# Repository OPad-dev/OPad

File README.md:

<div align="center">

<picture>
  <source media="(prefers-color-scheme: dark)" srcset="docs/assets/wordmark-dark.svg">
  
</picture>

### A low-latency three-key osu! keypad with a touchscreen, that is just a keyboard until you want more.

**[Download](https://github.com/OPad-dev/OPad/releases)** ·
**[Documentation](docs/index.md)** ·
[Get started](docs/start/what-you-need.md) ·
[Troubleshooting](docs/troubleshooting.md) ·
[Code signing policy](#code-signing-policy) ·
[Privacy](#privacy)

</div>

---

OPad turns a **Waveshare ESP32-S3-Touch-LCD-2** and two switches into a
competition-grade keypad for osu! and osu!lazer. It is a plain **1000 Hz USB
HID keyboard**: plug it into any Linux or Windows 10/11 machine and it types,
with no driver and no setup. The optional desktop app adds live gameplay stats
on the pad's screen, a screen designer, lifetime key counters, Hall Effect
calibration and one-click firmware updates.

## Highlights

|  |  |
|---|---|
| ⚡ **Latency always wins** | Keys go straight from the switch to the USB report. The screen, storage, tray and tosu are never on that path, and anything that measurably adds latency or jitter is cut. |
| 🔌 **Works with nothing installed** | Standard HID keyboard (`Z` / `X` by default). The desktop software only adds features. |
| 👆 **The touchscreen is a fourth button** | During a map a resting finger is Quick Retry. Outside a map, swipes change the volume or the track. |
| 📊 **Live telemetry** | With [tosu](https://github.com/KotRikD/tosu), the pad shows PP, accuracy, combo and more, in layouts you design yourself. |
| 🧲 **Mechanical or Hall Effect** | MX switches wired by hand, or the OPad V3 carrier with MX or Hall Effect modules, guided calibration and Rapid Trigger. |
| 🛟 **Can't be bricked by an update** | Updates go to the other flash slot and roll back on their own if the pad doesn't come back. No BOOT or RESET buttons, ever. |
| 🔁 **App and pad update independently** | Any app version talks to any pad version; they negotiate. |
| 🚫 **Every key comes from a finger** | No macros, auto-tap or host-injected keys. Not even as an option. |

## Quick start

1. **Wire two switches** between header **P2 pin 11** (GPIO 14, `Z`) /
   **pin 12** (GPIO 9, `X`) and **GND** (pin 13 or 2), or assemble the V3
   carrier. → [Wiring the keys](docs/build/wiring-the-keys.md)
2. **Plug it in.** It types immediately. → [First connection](docs/start/first-connection.md)
3. **Optional: install the app** for the screen, counters and updates.
   → [Install the app](docs/start/install-the-app.md)

| System | Download from [Releases](https://github.com/OPad-dev/OPad/releases) |
|---|---|
| Windows 10/11 | `OPad-Windows-Setup-<version>.exe` |
| Debian, Ubuntu, Pop!_OS | `OPad-Linux-Debian-Ubuntu-<version>.deb` |
| Fedora, RHEL, Alma, Rocky | `OPad-Linux-Fedora-<version>.rpm` |
| Arch | `OPad-Linux-Arch-<version>.pkg.tar.zst` |
| Any other Linux | `OPad-Linux-<version>.AppImage` |

> [!NOTE]
> The Windows installer is not code-signed yet, so SmartScreen warns about it
> (**More info → Run anyway**). Each release page lists the SHA-256 of every
> file if you'd rather verify the download. See the
> [code signing policy](#code-signing-policy).

## How it fits together

```mermaid
flowchart LR
    osu["osu! / osu!lazer"] -. read by .-> tosu["tosu"]
    tosu -- WebSocket --> daemon["opad-daemon<br/>settings · stats · updates"]
    gui["opad-gui<br/>tray · designer · diagnostics"] <-- IPC --> daemon
    cli["opadctl"] <-- IPC --> daemon
    daemon <-- "USB serial (CDC)" --> pad["OPad<br/>ESP32-S3 + 2&quot; touchscreen"]
    pad == "USB HID keyboard, 1000 Hz" ==> os["Your computer"]
```

The keyboard link (thick arrow) needs none of the boxes above it.
[Architecture](docs/explanation/architecture.md) explains the rest.

## Documentation

The full documentation lives in [`docs/`](docs/index.md) and is also
published as a website.

| | |
|---|---|
| 🚀 **Getting started** | [What you need](docs/start/what-you-need.md) · [Wiring](docs/build/wiring-the-keys.md) · [First connection](docs/start/first-connection.md) · [Install the app](docs/start/install-the-app.md) |
| 🧭 **Guides** | [Update firmware](docs/guides/update-firmware.md) · [Touchscreen & swipes](docs/guides/touchscreen-and-swipes.md) · [Screen layouts](docs/guides/customize-screen-layout.md) · [Hall Effect calibration](docs/guides/calibrate-hall-effect.md) · [tosu](docs/guides/use-with-tosu.md) · [Backup](docs/guides/backup-and-restore.md) |
| 🛟 **When something's wrong** | [Troubleshooting](docs/troubleshooting.md) · [Recovery & reflashing](docs/recovery.md) |
| 📖 **Reference** | [`opadctl`](docs/reference/opadctl.md) · [GUI](docs/reference/gui.md) · [Device settings](docs/reference/device-settings.md) · [Pinout](docs/reference/pinout.md) · [Serial protocol](docs/reference/serial-protocol.md) |
| 💡 **How it works** | [Architecture](docs/explanation/architecture.md) · [Latency](docs/explanation/latency.md) · [Updates & rollback](docs/explanation/updates-and-rollback.md) · [Hall Effect](docs/explanation/hall-effect.md) |
| 🛠️ **Contributing** | [Developer hub](docs/develop/index.md) · [Building](docs/develop/building.md) · [Testing](docs/develop/testing.md) · [AGENTS.md](AGENTS.md) |

Documentation is also available in [Spanish](docs/es/index.md).

## Building from source

```bash
# Desktop suite (daemon, GUI, opadctl)
cd desktop && cargo build --release

# Firmware (ESP-IDF v5.5.2)
cd firmware && idf.py set-target esp32s3 build

# Flash it over USB: the other OTA slot, rolls back if it never enumerates
opadctl pad flash firmware/build/opad-firmware.bin
```

System packages, `make install`, tests and CI are covered in
[Building from source](docs/develop/building.md) and
[Testing](docs/develop/testing.md). Contributions are welcome: read
[AGENTS.md](AGENTS.md) first. It holds the product rules every change keeps.

---

## Code signing policy

Free code signing provided by [SignPath.io](https://about.signpath.io), certificate by [SignPath Foundation](https://signpath.org).

The Windows programs (`opad-gui.exe`, `opad-daemon.exe`, `opadctl.exe`) and the Windows installer are built from this repository by GitHub Actions (`.github/workflows/release-app.yml`) and signed only after a maintainer approves each release. Until the SignPath Foundation certificate is in place, Windows releases are published unsigned.

- Committers and reviewers: [GFerreiroS](https://github.com/GFerreiroS)
- Approvers: [GFerreiroS](https://github.com/GFerreiroS)

The installer also contains two programs that are not built from this repository's code and are not signed by this project: `espflash.exe` ([esp-rs/espflash](https://github.com/esp-rs/espflash), the upstream release binary) and `tosu.exe` ([tosu](https://github.com/KotRikD/tosu), built from upstream source).

Privacy policy: see [Privacy](#privacy) below.

## Privacy

OPad collects no personal data and has no telemetry or analytics. The desktop app makes these network requests, and no others:

- **Update check**, once a day while the app's background service runs, and whenever you press *Check now*: it downloads the public release list from `https://updates.opad.dev/` (served by GitHub Pages). The request carries the app's version in its User-Agent (`opad/<version>`) and nothing about you or your pad. Turning off automatic updates in **Settings → Updates** stops installs, not this check.
- **Downloads** of an update you accept (or of tosu, if its automatic updates are on), from GitHub Releases.
- **tosu**, which the app runs, serves osu!'s game state on your own computer (`127.0.0.1`) and does not send it anywhere. When it starts, tosu asks GitHub whether a newer tosu exists; OPad turns its self-update off, so nothing is downloaded.

GitHub, which hosts the update list and the downloads, sees your IP address as it does for any website; see [GitHub's privacy statement](https://docs.github.com/site-policy/privacy-policies/github-general-privacy-statement). Everything the app stores (settings, statistics, backups) stays on your computer and your pad.

## Third-party software

OPad bundles or interacts with the following third-party software:

- **[tosu](https://github.com/KotRikD/tosu)** by Mikhail Babynichev and the tosu contributors, under the [LGPL-3.0](licenses/tosu/LICENSE) ([notice](licenses/tosu/NOTICE)). Under the LGPL you may replace the bundled tosu with your own build: point the `OPAD_TOSU_PATH` environment variable at it, or set an external path in the GUI under **Settings → tosu**.
- **[espflash](https://github.com/esp-rs/espflash)**, bundled with the desktop packages as the upstream release binary.

## Licence

OPad is free and open source, software and hardware:

- **Software**: the firmware, the desktop app (daemon, GUI, CLI), the protocol, the scripts and the documentation, under the [GNU General Public License v3.0 or later](LICENSE) (`GPL-3.0-or-later`).
- **Hardware**: everything in [`hardware/`](hardware/) (the PCB designs, footprints and symbols, the enclosure CAD and the production files), under the [CERN Open Hardware Licence v2, Strongly Reciprocal](hardware/LICENSE) (`CERN-OHL-S-2.0`). The scripts in `hardware/` that generate and check those files are software, under `GPL-3.0-or-later`.

You may build, modify and sell OPad. If you distribute a modified version, of the software or of the hardware, you must publish its source under the same licence. Every file's licence is recorded in [`REUSE.toml`](REUSE.toml).

Third-party components keep their own open licences and ship with their notices:

- [tosu](licenses/tosu/LICENSE) (LGPL-3.0), built from upstream source and bundled with the desktop packages, see above. Not stored in this repository.
- [Montserrat](desktop/gui/assets/fonts/Montserrat-OFL.txt) fonts embedded in the GUI (SIL Open Font License 1.1).
- [nanopb](firmware/main/protocol/nanopb/LICENSE.txt) protobuf runtime vendored in the firmware (zlib licence).

Libraries pulled in at build time (Rust crates, ESP-IDF components such as LVGL and TinyUSB) are not stored here and are used under their own permissive licences.

The firmware's easter-egg animation (`firmware/main/ui/easter_egg_gif.h`) is the one exception: it was made from images found online whose author and licence are unknown, and no rights to it are granted. If you hold the rights and want it credited or no longer used, open an issue or write to the contact in [`SECURITY.md`](SECURITY.md); it is then credited, or removed from the firmware ([`LICENSES/LicenseRef-Unknown-ThirdParty.txt`](LICENSES/LicenseRef-Unknown-ThirdParty.txt)).

## Trademark

OPad is an independent open-source hardware and software project. It is not affiliated with, endorsed by, or sponsored by ppy Pty Ltd or osu!. "osu!" is a registered trademark of ppy Pty Ltd.

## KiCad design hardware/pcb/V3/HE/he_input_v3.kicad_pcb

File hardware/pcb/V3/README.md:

# OPad V3 PCBs

| Board | Folder | Size | Status |
|---|---|---|---|
| Controller carrier V3 | `Carrier/` | 35.0 × 48.2 mm (the V1 outline plus a lug in the window for the USB cable) | Built; works on the bench (2026-11-20) |
| USB board V3 | `USB/` | 20.0 × 22.0 mm | Built; works on the bench (2026-11-20) |
| MX input module V3 | `MX/` | 71.05 × 24.0 mm, 3 keys | Built; works on the bench (2026-11-20) |
| HE input module V3 | `HE/` | 71.05 × 24.0 mm, 3 keys | Built; works on the bench (2026-11-20) |

These replace every V1/V2 board (decisions H10–H18 and section 4.2 in
`docs/specs/hardware-redesign-brief.md`). They are built and run on the owner's
bench with the firmware on `main`: board test, three keys on both modules, HE V3
calibration, key 3 and latency (`docs/testing-checklist.md` HW-06 to HW-15, and
`docs/history/2026-11-20-v3-modules-handoff.md`). An MX V3 module on a turned-over
module cable is not read; every pad ships with the type B cable.

## What is different from V1

- **Module cable:** a 14-way, 1.0 mm FFC replaces the JST SH 8-pin. It is reversible
  (a reversed cable only swaps signals between ESP32 pins, see Cables).
- **USB-C on its own board** at the case's rear wall (H18). It has ESD protection, a VBUS
  ferrite and capacitors, and a Schottky so a cable in the Waveshare's own port cannot
  feed this one. An 8-way FFC that reads the same from either end takes 5 V, D+ and D−
  to the carrier, which passes them to P1-14, P1-11 (GPIO20) and P1-12 (GPIO19).
  The case seats it on pins in its two M2 holes and clamps it from above; stops and the
  rear wall take the plug's push and pull, so the header sockets never do. The path is passive, so flashing and recovery work over it as over
  the Waveshare's own port.
- **The carrier's USB connector** sits on a lug in the window's USB-end rear corner,
  mouth on the USB-end edge: P1's sockets fill the rear edge, and the lug keeps clear of
  the M2 hole at the USB-end rear corner. (The V3 and V4 cases do not use that hole: the USB
  board lies under it, so a support presses the rear rail instead.)
- **Three keys** on both modules, and **four corner holes** for the case's locating pins.
- **HE:**
  - The ADC is an **ADS7028** (C880341), the ADS7038's sibling. It has the same pins,
    registers, averaging and CRC, and it is in JLCPCB's assembly stock. The ADS7038 is
    only on LCSC.
  - An **LP5907 LDO** powers the sensors and the ADC reference from the cable's 5 V,
    not from the Waveshare's buck-converter 3V3.
  - CS has a pull-up, and the SPI lines have ESD protection.
- **Every part is on one side:** the top of the carrier and the USB board, the bottom of
  the modules.

## Cables

### Module (14-way FFC, 1.0 mm, type B, 80 mm in the V3 and V4 cases)

| Contact | 1 | 2 | 3 | 4 | 5 | 6 | 7 | 8 | 9 | 10 | 11 | 12 | 13 | 14 |
|---|---|---|---|---|---|---|---|---|---|---|---|---|---|---|
| Carrier | GND | 5V | 3V3 | GPIO8 | GPIO6 | GND | GPIO2 | GPIO4 | GND | GPIO10 | GPIO7 | 3V3 | 5V | GND |
| HE | GND | 5V | 3V3 | ID | MISO | GND | SCLK | MOSI | GND | CS | – | 3V3 | 5V | GND |
| MX | GND | – | 3V3 | ID | KEY3 | GND | – | – | GND | KEY1 | KEY2 | 3V3 | – | GND |

A reversed cable connects contact k to 15 − k. Power and ground still meet power and
ground. The module's ID arrives on GPIO7 instead of GPIO8 (both are ADC1 pins), and the
firmware swaps the other pins in the GPIO matrix. `hardware/verify/tests/test_system.py`
follows every pin both ways round. MX keeps KEY1 = GPIO10 and KEY2 = GPIO7, as on V1.

Module IDs: MX V3 = 47k/100k = 2.24 V, HE V3 = 100k/100k = 1.65 V (the class HE V2
reserved, since the ADC and pins are the same). Firmware cut-offs: 0.68 / 1.35 / 1.95 / 2.6 V.

### USB (8-way FFC, 1.0 mm, type A, 80 mm in the V3 and V4 cases)

| Contact | 1 | 2 | 3 | 4 | 5 | 6 | 7 | 8 |
|---|---|---|---|---|---|---|---|---|
| USB board and carrier | GND | 5V | D− | D+ | D+ | D− | 5V | GND |

The pinout reads the same from either end, so a reversed cable (k to 9 − k) meets the
same nets. D+ and D− each use two conductors, joined on both boards. The two 5V contacts
carry 1 A together (0.5 A each, connector datasheet). The connectors are a different width
from the module's, so the two cables cannot be swapped. `test_system.py` follows the jack's
D+, D− and 5 V to GPIO20, GPIO19 and P1-14 with the cable both ways round.

## Checks (MX 2026-10-23; carrier, USB, HE 2026-10-29)

| Check | Carrier | USB | MX | HE |
|---|---|---|---|---|
| KiCad ERC, DRC with zones refilled, schematic parity | 0 | 0 | 0 | 0 |
| `hardware/verify` (fab files against the intended netlist, datasheet pin drawings, JLCPCB's own part models at the CPL) | 0 errors | 0 errors | 0 errors | 0 errors |
| `hardware/verify/tests/test_system.py` (cables both ways, ID margins) | all pass | all pass | all pass | all pass |

- **Ferrite C107335 (carrier, HE):** replaces C1002 (Sunlord GZ1608D601TF), which LCSC no
  longer lists (product page not found, 2026-10-29). Same 600 Ω @ 100 MHz, 1 A instead of
  200 mA. It is an Extended part at JLCPCB, so it adds a setup fee.

- **AFA07-S08 (C262714):** JLCPCB's model draws the fitting nails 3.3 mm tall and 0.63 mm
  nearer the contacts than the maker's drawing (the same drawing as the 14-way's). Our
  pads follow the drawing. The CPL is aligned on the contacts, and the model's nails are
  allowed 0.8 mm (`MECH_TOL` in `export_v3.py`, `jlc_mech_tol` in `devices.py`).

- **CPL:** `export_v3.py` writes the CPL by fitting JLCPCB's own footprint of every part
  onto our pads. Every polarised bottom-side part therefore sits at 0° or 180°. That
  is the case the evidence covers (`hardware/verify/opadverify/jlc.py`). For that reason
  the Hall sensors are turned a quarter from V1.1; the generator asserts that their pads
  are V1.1's layout rotated, never mirrored.
- **Sensor keepout:** a 3 × 3 mm copper keepout sits round each Hall sensor, as on V1.1.

## Files

```
V3/
├── lib/                 footprints (new ones drawn from the makers' drawings) and symbols
├── Carrier/ USB/ MX/ HE/  KiCad projects, route.json (stitching vias, power track widths), production/
└── scripts/
    ├── v3lib.py         library: footprints, symbols
    ├── generate_v3.py   schematics and placed boards (overwrites the routing)
    ├── route_v3.py      Freerouting 1.9.0, retried until DRC has no error and nothing unconnected
    └── export_v3.py     V1's export_production.py checks and files, with the JLCPCB-model CPL
```

```
python3 hardware/pcb/V3/scripts/generate_v3.py [carrier] [usb] [mx] [he]
python3 hardware/pcb/V3/scripts/route_v3.py Carrier|USB|MX|HE
python3 hardware/pcb/V3/scripts/export_v3.py [Carrier] [USB] [MX] [HE]
cd hardware/verify && ../../.tools/venv/bin/python -m opadverify golden/he_v3.toml   # and carrier_v3, usb_v3, mx_v3
```

## Before ordering more

1. **Case:** `hardware/3d/custom_case/V3` was printed and fits these boards; the
   latest small changes to it have not been printed. `hardware/3d/custom_case/V4`, the
   case to ship, is V3 inside a new outside: its fit check passes, it is not printed yet.
2. **JLCPCB preview:** check every part sits on its pads before paying. The checker
   predicts no turning is needed (`-v` prints where pin 1 of each polarised part must be).

## Parts (JLCPCB, all in assembly stock on 2026-10-23)

| Board | Part | LCSC |
|---|---|---|
| carrier, MX, HE | JUSHUO AFA07-S14FCA-00 FFC connector | C262720 |
| carrier, USB | JUSHUO AFA07-S08FCA-00 FFC connector (in stock 2026-10-28) | C262714 |
| USB | HRO TYPE-C-31-M-12 USB-C | C165948 |
| carrier | XUNPU FH2.54-09-14PZD 1×14 socket, 8.5 mm (×2) | C7500781 |
| carrier, USB, HE | ProTek SRV05-4-P-T7 ESD array | C85364 |
| USB | Murata BLM18PG121SN1D ferrite, 2 A | C14709 |
| USB | B5817W Schottky (JLCPCB's model: pad 1 anode, pad 2 cathode) | C7420328 |
| carrier, HE | TDK MPZ1608S601ATA00 ferrite, 1 A | C107335 |
| MX | Kailh CPG151101S11 hot-swap socket (×3) | C41430893 |
| HE | TI DRV5055A3QDBZR Hall sensor (×3) | C266128 |
| HE | TI ADS7028IRTER ADC | C880341 |
| HE | TI LP5907MFX-3.3 LDO | C80670 |

The full lists, with the passives, are in each board's `production/jlcpcb/*-BOM-JLCPCB.csv`.
The cables are not assembled. The connectors are bottom contact, so the cable type is
fixed by the route in the V3 case (`hardware/3d/custom_case/V3/README.md`, The cables):
a 14-way, 1.0 mm FFC, **type B** (contacts on opposite sides, "reverse"), 80 mm
(LCSC C54350068), and an
8-way, 1.0 mm FFC, **type A** (contacts on the same side), 80 mm (LCSC C54350099; the route is about 66 mm with
both ends in their connectors, and the extra bows up in the space beside the stack).

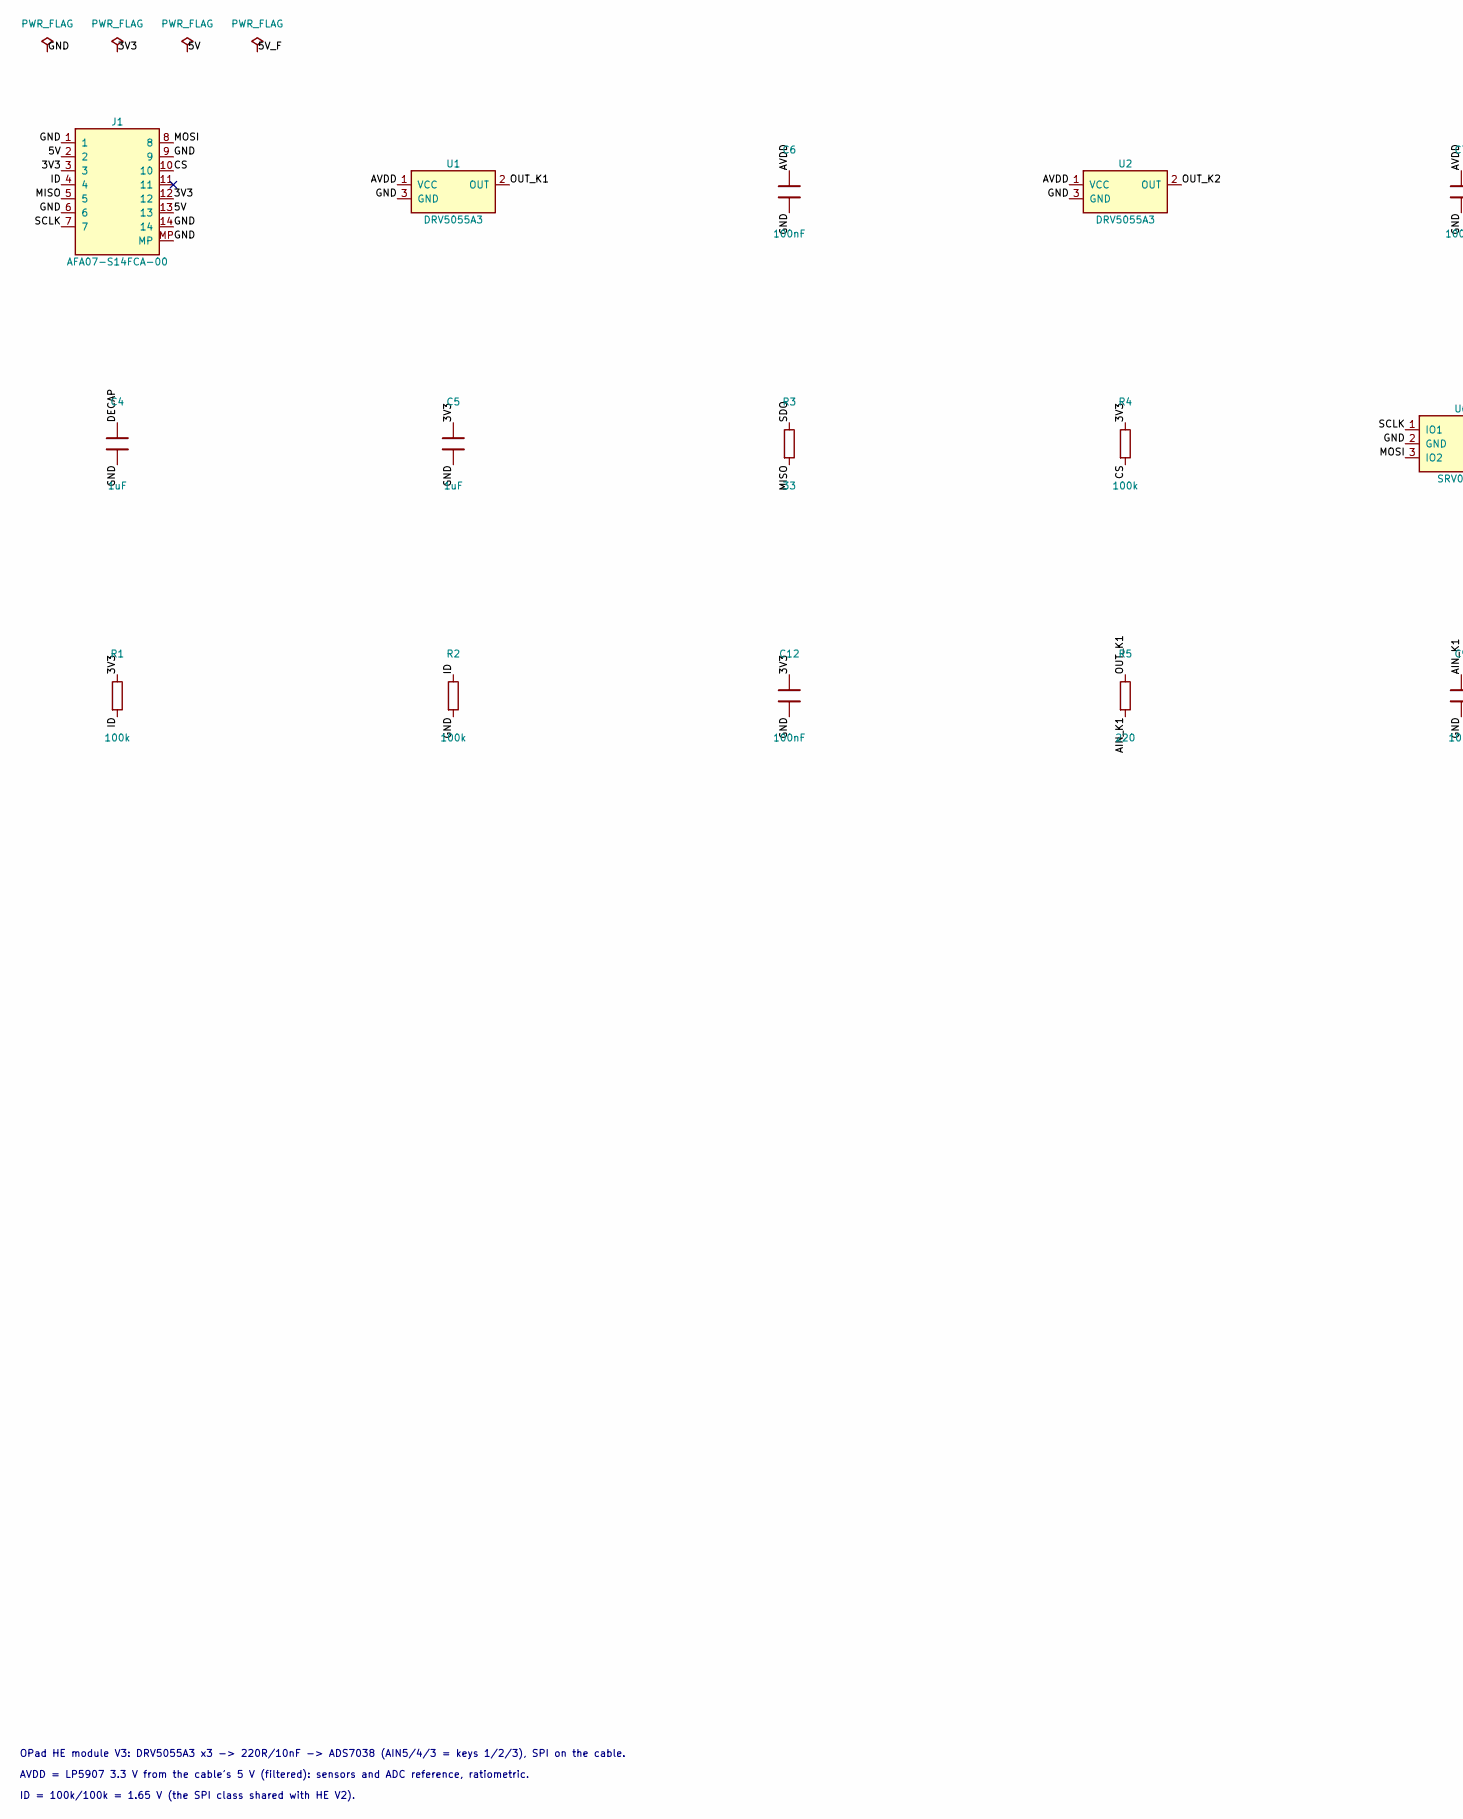
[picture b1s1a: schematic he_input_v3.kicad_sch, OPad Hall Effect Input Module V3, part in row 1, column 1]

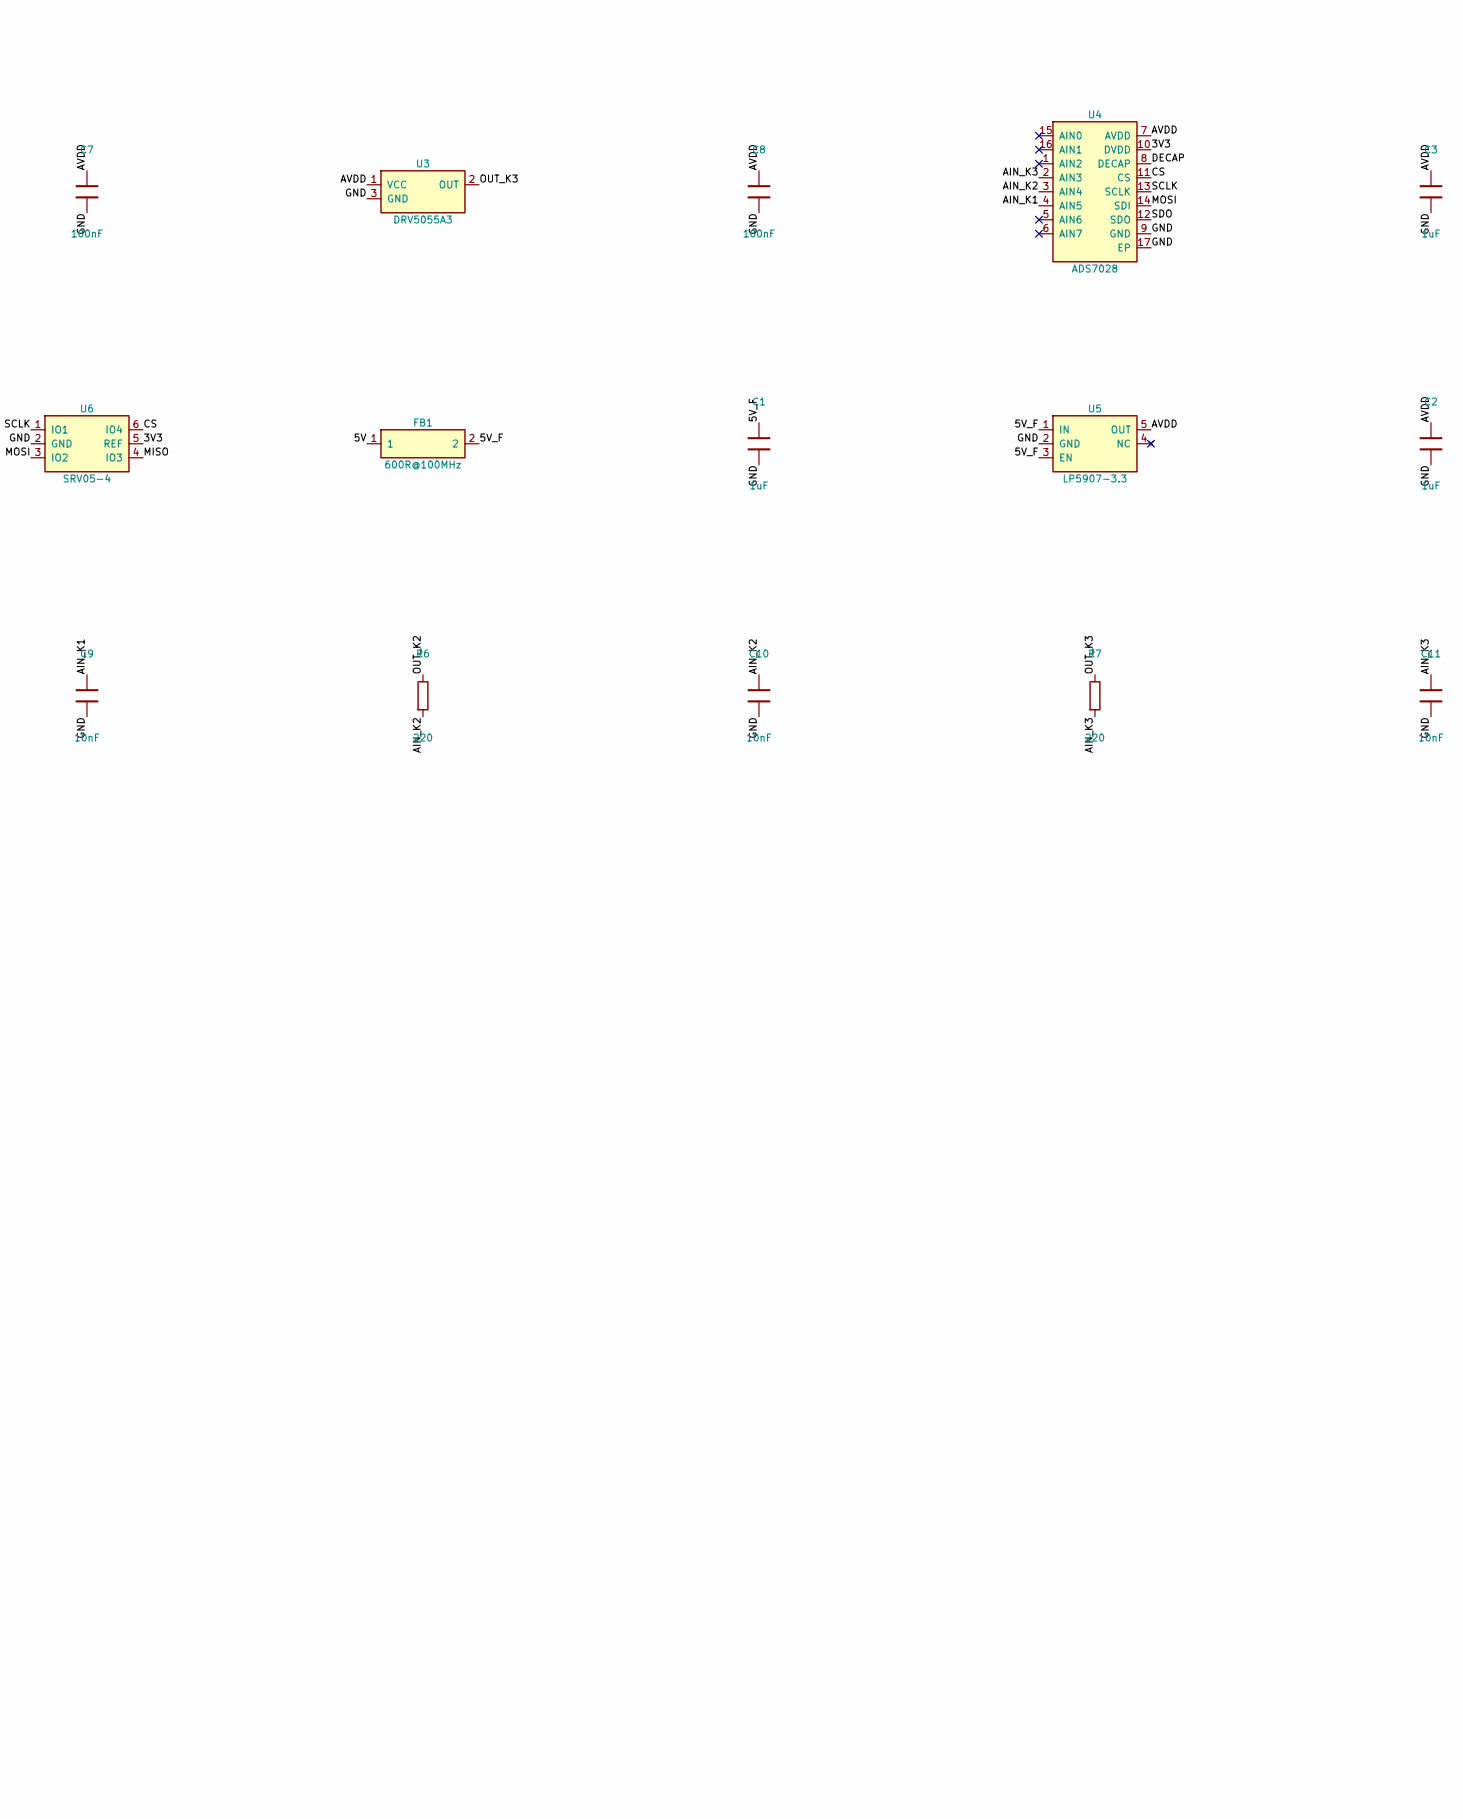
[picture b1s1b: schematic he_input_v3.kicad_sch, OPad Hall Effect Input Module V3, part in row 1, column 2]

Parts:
C1, C2, C3, C4, C5: 1uF; C_0603_1608Metric; MPN Samsung CL10A105KB8NNNC; LCSC C15849
C6, C7, C8, C12: 100nF; C_0603_1608Metric; MPN YAGEO CC0603KRX7R9BB104; LCSC C14663
C9, C10, C11: 10nF; C_0603_1608Metric; MPN FH 0603B103K500NT; LCSC C57112
FB1: 600R@100MHz; L_0603_1608Metric; MPN TDK MPZ1608S601ATA00; LCSC C107335
J1: AFA07-S14FCA-00; FFC_JUSHUO_AFA07-S14FCA_1x14-1MP_P1.0mm_Horizontal; MPN JUSHUO AFA07-S14FCA-00; LCSC C262720
R1, R2, R4: 100k; R_0603_1608Metric; MPN UNI-ROYAL 0603WAF1003T5E; LCSC C25803
R3: 33; R_0603_1608Metric; MPN UNI-ROYAL 0603WAF330JT5E; LCSC C23140
R5, R6, R7: 220; R_0603_1608Metric; MPN UNI-ROYAL 0603WAF2200T5E; LCSC C22962
U1, U2, U3: DRV5055A3; SOT-23; MPN Texas Instruments DRV5055A3QDBZR; LCSC C266128
U4: ADS7028; WQFN-16-1EP_3x3mm_P0.5mm_EP1.68mm; MPN Texas Instruments ADS7028IRTER; LCSC C880341
U5: LP5907-3.3; SOT-23-5; MPN Texas Instruments LP5907MFX-3.3/NOPB; LCSC C80670
U6: SRV05-4; SOT-23-6; MPN ProTek SRV05-4-P-T7; LCSC C85364

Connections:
/3V3: C5.1, C12.1, J1.3, J1.12, R1.1, R4.1, U4.10 (DVDD), U6.5 (REF)
/5V: FB1.1, J1.2, J1.13
/5V_F: C1.1, FB1.2, U5.1 (IN), U5.3 (EN)
/AIN_K1: C9.1, R5.2, U4.4 (AIN5)
/AIN_K2: C10.1, R6.2, U4.3 (AIN4)
/AIN_K3: C11.1, R7.2, U4.2 (AIN3)
/AVDD: C2.1, C3.1, C6.1, C7.1, C8.1, U1.1 (VCC), U2.1 (VCC), U3.1 (VCC), U4.7 (AVDD), U5.5 (OUT)
/CS: J1.10, R4.2, U4.11 (CS), U6.6 (IO4)
/DECAP: C4.1, U4.8 (DECAP)
/GND: C1.2, C2.2, C3.2, C4.2, C5.2, C6.2, C7.2, C8.2, C9.2, C10.2, C11.2, C12.2, J1.1, J1.6, J1.9, J1.14, J1.MP, R2.2, U1.3 (GND), U2.3 (GND), U3.3 (GND), U4.9 (GND), U4.17 (EP), U5.2 (GND), U6.2 (GND)
/ID: J1.4, R1.2, R2.1
/MISO: J1.5, R3.2, U6.4 (IO3)
/MOSI: J1.8, U4.14 (SDI), U6.3 (IO2)
/OUT_K1: R5.1, U1.2 (OUT)
/OUT_K2: R6.1, U2.2 (OUT)
/OUT_K3: R7.1, U3.2 (OUT)
/SCLK: J1.7, U4.13 (SCLK), U6.1 (IO1)
/SDO: R3.1, U4.12 (SDO)

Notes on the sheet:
OPad HE module V3: DRV5055A3 x3 -> 220R/10nF -> ADS7038 (AIN5/4/3 = keys 1/2/3), SPI on the cable.
AVDD = LP5907 3.3 V from the cable's 5 V (filtered): sensors and ADC reference, ratiometric.
ID = 100k/100k = 1.65 V (the SPI class shared with HE V2).

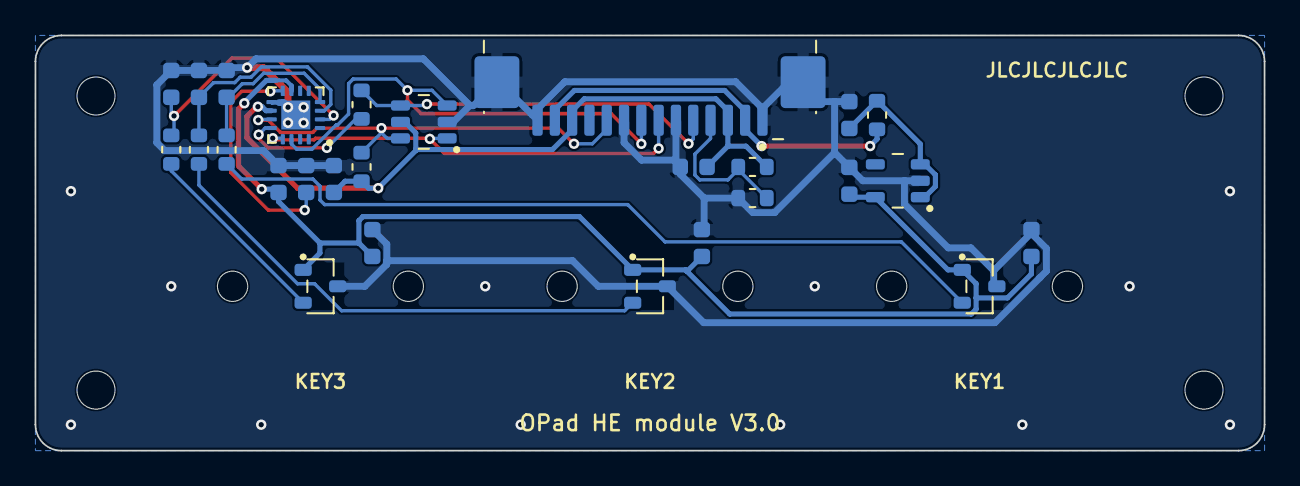
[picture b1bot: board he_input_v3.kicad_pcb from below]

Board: 2 copper layers, 71.0 x 24.0 mm, 34 parts (27 on the bottom side), 18 nets.

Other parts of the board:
H1, H2, H3, H4: MountingHole_2.2mm_M2
SW1, SW2, SW3: SW_MX_Hall_SolidCentre; SW_MX_Hall_PlateMount_SolidCentre

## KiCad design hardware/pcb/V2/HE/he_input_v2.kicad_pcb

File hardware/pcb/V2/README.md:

# OPad V2 PCBs

| Board | Folder | Size | Status |
|---|---|---|---|
| **Hall Effect input module V2** | `HE/` | 71.05 × 24.0 mm | **Prototype, not built yet.** Firmware support not written yet (see Firmware) |

The carrier and the MX module stay at V1 (`hardware/pcb/V1/`); nothing on them changes. V2 replaces the V1.1 HE module, which is deprecated once V2 works.

## What changed from HE V1.1, and why

The V1.1 module sent the sensors' analog voltages through the cable to the ESP32-S3's own ADC. That made two kinds of noise (`docs/history/2026-10-22-he-phantom-presses.md`):

- **Constant fuzz** of ±30–40 counts per reading, from the ESP32-S3's ADC itself. The module ID resistor divider, which has no sensor, showed the same amount, and the key and ID noise did not move together (correlation +0.08).
- **Phantom spikes** of +60 to +380 counts lasting about 70 µs to 1 ms, from outside the module (USB cable or PC side), getting into the analog signals.

V2 measures the sensors **on the module** and sends numbers over SPI, so neither reaches the measurement:

| Change | Part | Why |
|---|---|---|
| ADC on the module | TI **ADS7038** (U4), 8-channel 12-bit SAR, SPI, WQFN-16 3 × 3 mm | Its reference is its own AVDD, which also powers the sensors, so the reading is **ratiometric**: a supply wobble moves the sensor output and the ADC's ruler together. It averages internally and returns 16-bit results, so the ESP32 does not have to read it more often. Only digital SPI crosses the cable. |
| Sensor supply filter | Ferrite bead FB1 (600 Ω at 100 MHz) + 10 µF C2, 100 nF at each sensor, 1 µF at the ADC's AVDD | Keeps spikes on 3V3 away from the sensors and the reference |
| Output filter per sensor | 220 Ω series + 10 nF shunt, at the ADC | TI requires a resistor before any capacitor on the DRV5055 output (datasheet §7.1.3); the 10 nF also feeds the ADC's 12 pF sampling capacitor (ADS7038 datasheet §7.3.1). Time constant 2.2 µs, so it adds no noticeable delay |
| Three keys | U1–U3 at 19.05 mm pitch | For players who do not use the middle finger as one of two keys |

Kept from V1.1:
- **Sensor:** DRV5055**A3**, bipolar, so a switch with its magnet flipped still reads (the reading goes down instead of up).
- **Sensor position:** bottom side, on the key centres, with a 3 × 3 mm copper keepout on both layers.
- **Switch standard:** the Lekker one (V1 README, "Sensor architecture").
- **Assembly:** every part on the bottom side, so JLCPCB assembles one side.

## Connector (JST SH 8-pin, V1 pinout, same cable and carrier)

| Pin | Carrier GPIO | V1.1 HE | **V2** |
|---|---|---|---|
| 1 | 3V3 | sensor supply | 3V3 → FB1 → AVDD; ADC DVDD |
| 2 | GND | ground | ground |
| 3 | GPIO10 | analog key 1 | **SPI CS** |
| 4 | GPIO7 | analog key 2 | spare, to probe pad TP1 |
| 5 | GPIO8 | ID 1.06 V | **ID 1.65 V** (100k/100k, the "Hall SPI" ID the V1 README reserved) |
| 6 | GPIO6 | probe pad | **SPI MISO** (ADC SDO through 33 Ω R3) |
| 7 | GPIO4 | probe pad | **SPI MOSI** (ADC SDI) |
| 8 | GPIO2 | probe pad | **SPI SCLK** |

ADC channels: key 1 = AIN5, key 2 = AIN4, key 3 = AIN3 (`KEY_CH` in `scripts/generate_he_v2.py`). AIN0–AIN2, AIN6 and AIN7 are unused.

## Firmware (not written yet)

V2 needs a new HE input driver before it does anything:
- **Detection:** ID 1.65 V. Until the driver exists, firmware that does not know this ID must treat the module as unknown and never as an analog HE module.
- **Reading:** SPI on GPIO10/6/4/2 to the ADS7038, auto-sequence of the three channels with averaging.
- **Third key:** the keypress path, the protocol and the app all handle two keys today.
- **Board test:** pins 6–8 become SPI, so its spare-line check must change.

## Mechanics

- **Outline:** 71.05 × 24.0 mm, 1.5 mm corners, 1.6 mm FR-4, 2 layers. 16.475 mm from each outer key centre to the board edge, as on V1.
- **Keys:** KiCad (128.475, 83.5), (147.525, 83.5), (166.575, 83.5). Plate-mount peg holes 1.75 mm at ±5.08 mm on each key.
- **Mounting holes:** 2.2 mm (M2) at (115.5, 83.5) and (179.55, 83.5), 3.5 mm from each end on the key axis.
- **J1:** centred on the middle key at the rear edge, at the V1 offset from the key line, so the same 100 mm cable reaches it.
- **The V1.1 case does not fit:** its key deck has two keys and a 52 mm module. A three-key case is needed.

## Files and toolchain

```
V2/
├── README.md
├── lib/                       opad.pretty + opad.kicad_sym: the V1 parts used, plus
│                              WQFN-16 (TI RTE0016C land pattern), L_0603, ADS7038, FerriteBead
├── HE/he_input_v2.*           KiCad 10 project, schematic, routed board
│   └── production/            exports (see below)
└── scripts/
    ├── generate_he_v2.py      library, schematic and placed board (overwrites them)
    ├── route_he_v2.py         Freerouting, then GND stitching vias, then zone refill
    └── export_v2.py           ERC + DRC + parity, then the fab files (reuses V1's export_production.py)
```

To rebuild (needs KiCad 10's `pcbnew` Python module and Java):

```
python3 hardware/pcb/V2/scripts/generate_he_v2.py   # placed, unrouted board
python3 hardware/pcb/V2/scripts/route_he_v2.py      # routes it (Freerouting 1.9.0)
python3 hardware/pcb/V2/scripts/export_v2.py        # checks, then hardware/pcb/V2/HE/production/
```

- `route_he_v2.py` routes a copy without zones, because Freerouting treats pours and rule areas as obstacles. It then adds the stitching vias that clear the routed copper and refills the zones.
- Freerouting 2.1.0 routes this board completely and then hangs without writing the result, so the script uses 1.9.0 (`FREEROUTING_JAR`, default `~/.kicad-mcp/freerouting-1.9.0.jar`).
- Re-running `generate_he_v2.py` discards the routing.

Checked on 2026-10-23: ERC 0, DRC 0 violations and 0 unconnected with zones refilled, schematic parity clean. U1–U3 and J1 have the same pad layout and the same CPL rotations (180° and 0°, bottom) as the built V1.1 board.

## Ordering (JLCPCB)

Upload from `HE/production/jlcpcb/`:
- `he_input_v2-gerbers.zip` for the bare board;
- `he_input_v2-BOM-JLCPCB.csv` and `he_input_v2-CPL-JLCPCB.csv` for assembly.

Order options:
- 2 layers, 1.6 mm, HASL or ENIG;
- min track and spacing 0.2 / 0.15 mm (JLCPCB's standard process does 0.1 / 0.1);
- vias 0.6 mm with a 0.3 mm hole;
- assembly side **Bottom**;
- for the order-number marker, "Specify a location": `JLCJLCJLCJLC` on the bottom silkscreen.

| Designator | Part | LCSC |
|---|---|---|
| U1, U2, U3 | TI DRV5055A3QDBZR linear Hall sensor, SOT-23 | C266128 |
| U4 | TI ADS7038QRTERQ1, WQFN-16 3 × 3 mm (automotive grade of the ADS7038, same die and pinout; the commercial ADS7038IRTER, C2871580, had 8 in stock on 2026-10-23) | C2876384 |
| J1 | JST SM08B-SRSS-TB | C160407 |
| FB1 | Sunlord GZ1608D601TF ferrite bead, 600 Ω at 100 MHz, 0603 | C1002 |
| C1, C6, C7, C8 | 100 nF 50 V X7R 0603 | C14663 |
| C2 | 10 µF 10 V X5R 0603 | C19702 |
| C3, C4, C5 | 1 µF 50 V X5R 0603 | C15849 |
| C9, C10, C11 | 10 nF 50 V X7R 0603 | C57112 |
| R1, R2 | 100 kΩ 1 % 0603 | C25803 |
| R3 | 33 Ω 5 % 0603 | C23140 |
| R5, R6, R7 | 220 Ω 1 % 0603 | C22962 |

Every LCSC number above was checked against its LCSC product page on 2026-10-23 (title, maker and part number), because V1 once shipped with a wrong one (V1 README, Ordering). TP1 is a bare probe pad: it is not in the BOM or the CPL.

**Before paying, check JLCPCB's placement preview:**
- **U1–U3:** the single lead (pin 3, GND) points to the board's front edge, as on V1.1. The generator asserts the same pad layout as the built V1.1 board.
- **U4:** pin 1 at the silkscreen dot.
- **J1:** contacts towards the inside of the board, opening at the rear edge.

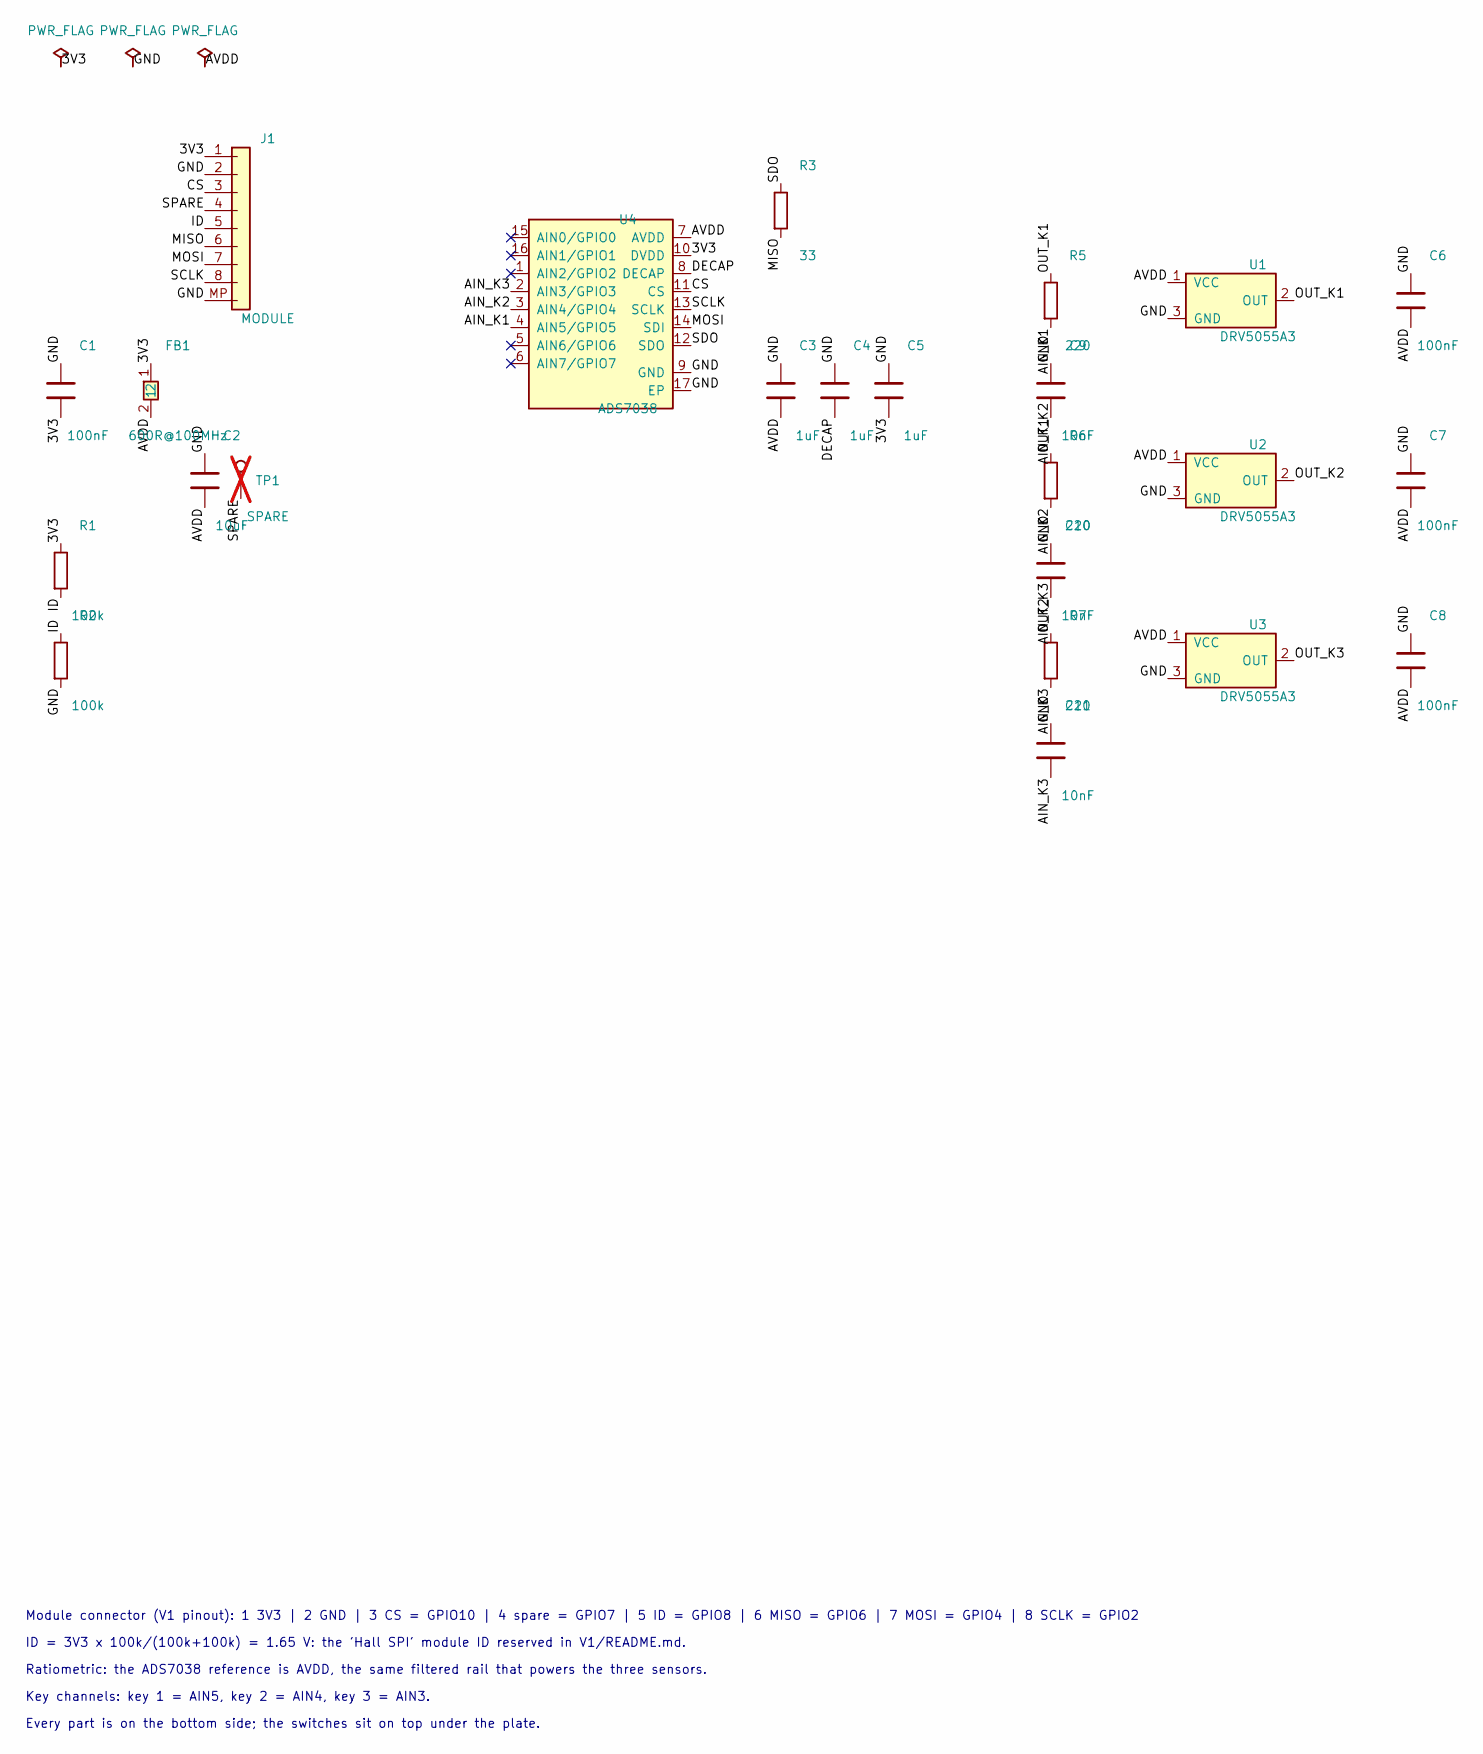
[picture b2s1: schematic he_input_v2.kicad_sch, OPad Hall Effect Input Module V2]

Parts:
C1, C6, C7, C8: 100nF; C_0603_1608Metric; MPN YAGEO CC0603KRX7R9BB104; LCSC C14663
C2: 10uF; C_0603_1608Metric; MPN Samsung CL10A106KP8NNNC; LCSC C19702
C3, C4, C5: 1uF; C_0603_1608Metric; MPN Samsung CL10A105KB8NNNC; LCSC C15849
C9, C10, C11: 10nF; C_0603_1608Metric; MPN FH 0603B103K500NT; LCSC C57112
FB1: 600R@100MHz; L_0603_1608Metric; MPN Sunlord GZ1608D601TF; LCSC C1002
J1: MODULE; JST_SH_SM08B-SRSS-TB_1x08-1MP_P1.00mm_Horizontal; MPN JST SM08B-SRSS-TB(LF)(SN); LCSC C160407
R1, R2: 100k; R_0603_1608Metric; MPN UNI-ROYAL 0603WAF1003T5E; LCSC C25803
R3: 33; R_0603_1608Metric; MPN UNI-ROYAL 0603WAF330JT5E; LCSC C23140
R5, R6, R7: 220; R_0603_1608Metric; MPN UNI-ROYAL 0603WAF2200T5E; LCSC C22962
TP1: SPARE; TestPoint_Pad_1.0x1.0mm; not fitted
U1, U2, U3: DRV5055A3; SOT-23; MPN Texas Instruments DRV5055A3QDBZR; LCSC C266128
U4: ADS7038; WQFN-16-1EP_3x3mm_P0.5mm_EP1.68mm; MPN Texas Instruments ADS7038QRTERQ1; LCSC C2876384

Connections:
/3V3: C1.2, C5.2, FB1.1, J1.1, R1.1, U4.10 (DVDD)
/AIN_K1: C9.2, R5.2, U4.4 (AIN5/GPIO5)
/AIN_K2: C10.2, R6.2, U4.3 (AIN4/GPIO4)
/AIN_K3: C11.2, R7.2, U4.2 (AIN3/GPIO3)
/AVDD: C2.2, C3.2, C6.2, C7.2, C8.2, FB1.2, U1.1 (VCC), U2.1 (VCC), U3.1 (VCC), U4.7 (AVDD)
/CS: J1.3, U4.11 (CS)
/DECAP: C4.2, U4.8 (DECAP)
/GND: C1.1, C2.1, C3.1, C4.1, C5.1, C6.1, C7.1, C8.1, C9.1, C10.1, C11.1, J1.2, J1.MP, R2.2, U1.3 (GND), U2.3 (GND), U3.3 (GND), U4.9 (GND), U4.17 (EP)
/ID: J1.5, R1.2, R2.1
/MISO: J1.6, R3.2
/MOSI: J1.7, U4.14 (SDI)
/OUT_K1: R5.1, U1.2 (OUT)
/OUT_K2: R6.1, U2.2 (OUT)
/OUT_K3: R7.1, U3.2 (OUT)
/SCLK: J1.8, U4.13 (SCLK)
/SDO: R3.1, U4.12 (SDO)
/SPARE: J1.4, TP1.1

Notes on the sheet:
Module connector (V1 pinout): 1 3V3 | 2 GND | 3 CS = GPIO10 | 4 spare = GPIO7 | 5 ID = GPIO8 | 6 MISO = GPIO6 | 7 MOSI = GPIO4 | 8 SCLK = GPIO2
ID = 3V3 x 100k/(100k+100k) = 1.65 V: the 'Hall SPI' module ID reserved in V1/README.md.
Ratiometric: the ADS7038 reference is AVDD, the same filtered rail that powers the three sensors.
Key channels: key 1 = AIN5, key 2 = AIN4, key 3 = AIN3.
Every part is on the bottom side; the switches sit on top under the plate.

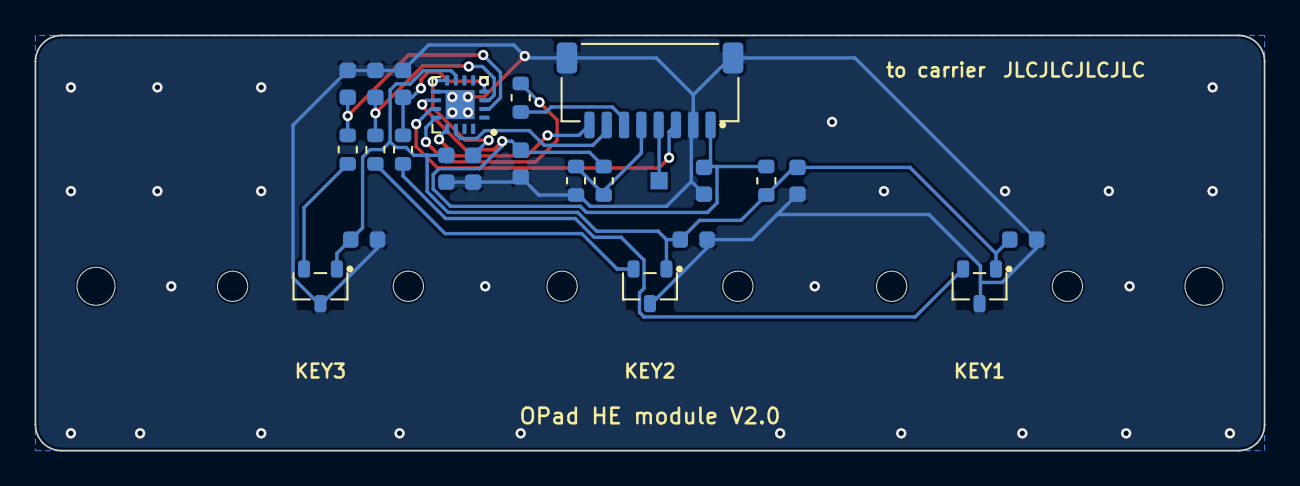
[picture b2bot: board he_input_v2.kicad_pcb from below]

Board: 2 copper layers, 71.0 x 24.0 mm, 29 parts (24 on the bottom side), 17 nets.

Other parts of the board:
H1, H2: MountingHole_2.2mm_M2
SW1, SW2, SW3: SW_MX_Hall_SolidCentre; SW_MX_Hall_PlateMount_SolidCentre

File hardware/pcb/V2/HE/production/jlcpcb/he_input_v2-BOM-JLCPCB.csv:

Comment,Designator,Footprint,LCSC Part #,MPN,Quantity
100nF,"C1,C6,C7,C8",C_0603_1608Metric,C14663,YAGEO CC0603KRX7R9BB104,4
10uF,C2,C_0603_1608Metric,C19702,Samsung CL10A106KP8NNNC,1
1uF,"C3,C4,C5",C_0603_1608Metric,C15849,Samsung CL10A105KB8NNNC,3
10nF,"C9,C10,C11",C_0603_1608Metric,C57112,FH 0603B103K500NT,3
600R@100MHz,FB1,L_0603_1608Metric,C1002,Sunlord GZ1608D601TF,1
MODULE,J1,JST_SH_SM08B-SRSS-TB_1x08-1MP_P1.00mm_Horizontal,C160407,JST SM08B-SRSS-TB(LF)(SN),1
100k,"R1,R2",R_0603_1608Metric,C25803,UNI-ROYAL 0603WAF1003T5E,2
33,R3,R_0603_1608Metric,C23140,UNI-ROYAL 0603WAF330JT5E,1
220,"R5,R6,R7",R_0603_1608Metric,C22962,UNI-ROYAL 0603WAF2200T5E,3
DRV5055A3,"U1,U2,U3",SOT-23,C266128,Texas Instruments DRV5055A3QDBZR,3
ADS7038,U4,WQFN-16-1EP_3x3mm_P0.5mm_EP1.68mm,C2876384,Texas Instruments ADS7038QRTERQ1,1

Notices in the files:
README.md:
https://img.shields.io/badge/software-GPL--3.0--or--later-2A1C6E
hardware/pcb/V1/README.md:
- **Library:** every part in `lib/` is OPad's own drawing under the hardware's CERN-OHL-S-2.0 licence (`hardware/LICENSE`).
